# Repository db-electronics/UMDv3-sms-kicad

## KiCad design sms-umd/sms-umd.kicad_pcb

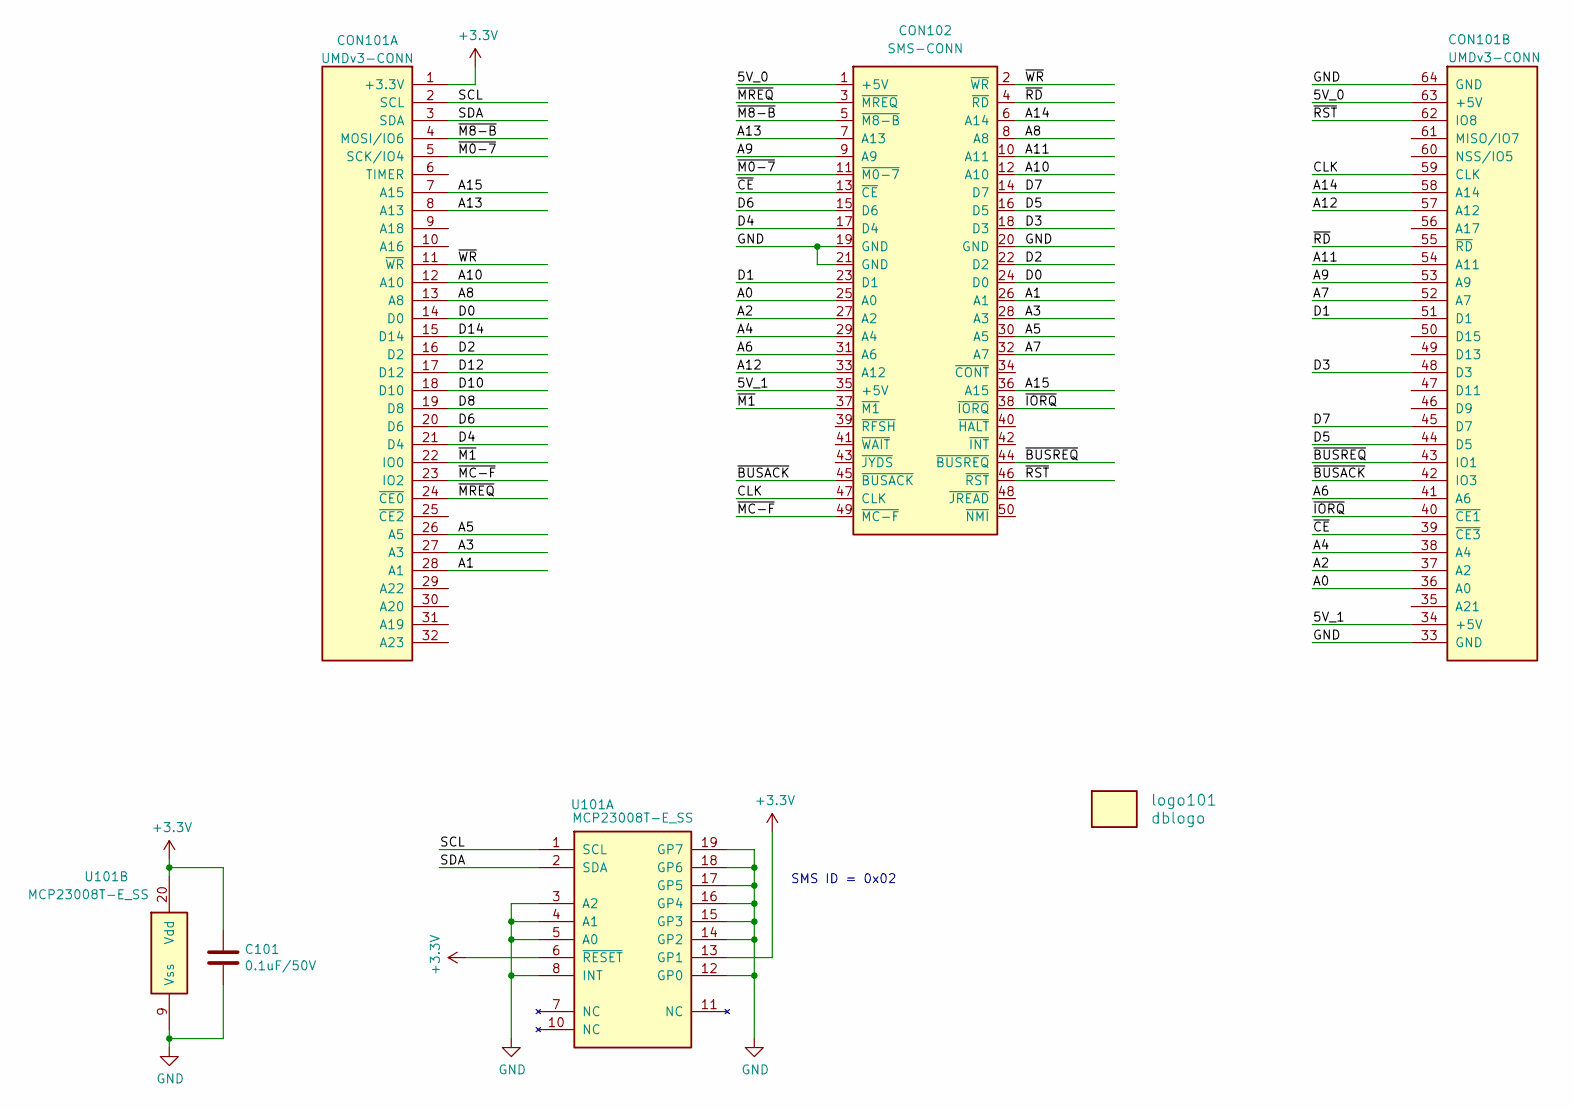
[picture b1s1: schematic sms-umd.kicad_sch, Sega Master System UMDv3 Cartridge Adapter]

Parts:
C101: 0.1uF/50V; 0603; Digikey 478-5052-1-ND
CON101: UMDv3-CONN; UMDv3-CONN-DIP64; Digikey SAM1211-32-ND
CON102: SMS-CONN; Digikey A31718-ND
U101: MCP23008T-E_SS; SSOP-20; Digikey MCP23008T-E/SSCT-ND
logo101: dblogo; db-logo_10mm

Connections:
+3V3: C101.1, CON101.1 (+3.3V), U101.6 (~RESET), U101.13 (GP1), U101.20 (Vdd)
/5V_0: CON101.63 (+5V), CON102.1 (+5V)
/5V_1: CON101.34 (+5V), CON102.35 (+5V)
/A0: CON101.36 (A0), CON102.25 (A0)
/A1: CON101.28 (A1), CON102.26 (A1)
/A2: CON101.37 (A2), CON102.27 (A2)
/A3: CON101.27 (A3), CON102.28 (A3)
/A4: CON101.38 (A4), CON102.29 (A4)
/A5: CON101.26 (A5), CON102.30 (A5)
/A6: CON101.41 (A6), CON102.31 (A6)
/A7: CON101.52 (A7), CON102.32 (A7)
/A8: CON101.13 (A8), CON102.8 (A8)
/A9: CON101.53 (A9), CON102.9 (A9)
/A10: CON101.12 (A10), CON102.12 (A10)
/A11: CON101.54 (A11), CON102.10 (A11)
/A12: CON101.57 (A12), CON102.33 (A12)
/A13: CON101.8 (A13), CON102.7 (A13)
/A14: CON101.58 (A14), CON102.6 (A14)
/A15: CON101.7 (A15), CON102.36 (A15)
/CLK: CON101.59 (CLK), CON102.47 (CLK)
/D0: CON101.14 (D0), CON102.24 (D0)
/D1: CON101.51 (D1), CON102.23 (D1)
/D2: CON101.16 (D2), CON102.22 (D2)
/D3: CON101.48 (D3), CON102.18 (D3)
/D4: CON101.21 (D4), CON102.17 (D4)
/D5: CON101.44 (D5), CON102.16 (D5)
/D6: CON101.20 (D6), CON102.15 (D6)
/D7: CON101.45 (D7), CON102.14 (D7)
/D8: CON101.19 (D8)
/D10: CON101.18 (D10)
/D12: CON101.17 (D12)
/D14: CON101.15 (D14)
/SCL: CON101.2 (SCL), U101.1 (SCL)
/SDA: CON101.3 (SDA), U101.2 (SDA)
/~BUSACK: CON101.42 (IO3), CON102.45 (~BUSACK)
/~BUSREQ: CON101.43 (IO1), CON102.44 (~BUSREQ)
/~CE: CON101.39 (~CE3), CON102.13 (~CE)
/~IORQ: CON101.40 (~CE1), CON102.38 (~IORQ)
/~M0-7: CON101.5 (SCK/IO4), CON102.11 (~M0-7)
/~M1: CON101.22 (IO0), CON102.37 (~M1)
/~M8-B: CON101.4 (MOSI/IO6), CON102.5 (~M8-B)
/~MC-F: CON101.23 (IO2), CON102.49 (~MC-F)
/~MREQ: CON101.24 (~CE0), CON102.3 (~MREQ)
/~RD: CON101.55 (~RD), CON102.4 (~RD)
/~RST: CON101.62 (IO8), CON102.46 (~RST)
/~WR: CON101.11 (~WR), CON102.2 (~WR)
GND: C101.2, CON101.33 (GND), CON101.64 (GND), CON102.19 (GND), CON102.20 (GND), CON102.21 (GND), U101.3 (A2), U101.4 (A1), U101.5 (A0), U101.8 (INT), U101.9 (Vss), U101.12 (GP0), U101.14 (GP2), U101.15 (GP3), U101.16 (GP4), U101.17 (GP5), U101.18 (GP6), U101.19 (GP7)

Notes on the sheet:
SMS ID = 0x02

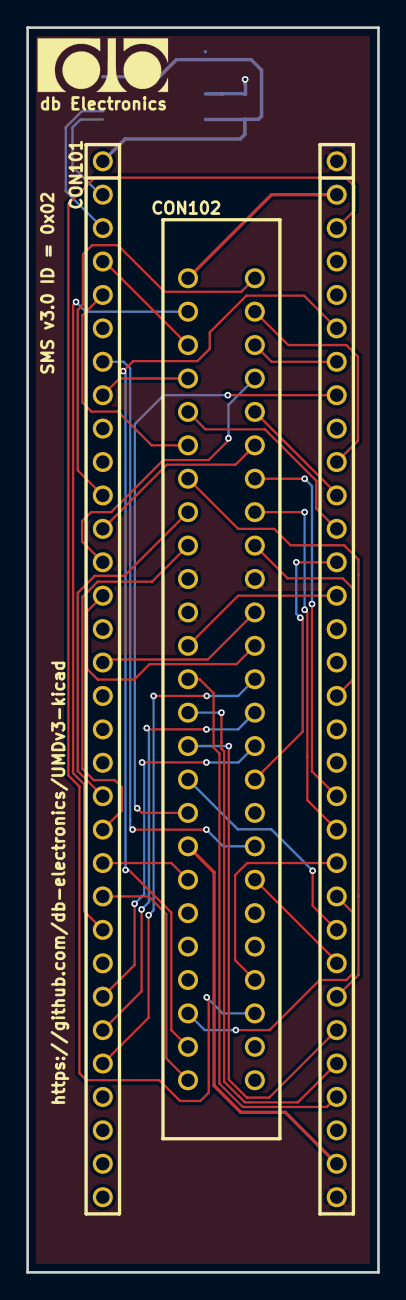
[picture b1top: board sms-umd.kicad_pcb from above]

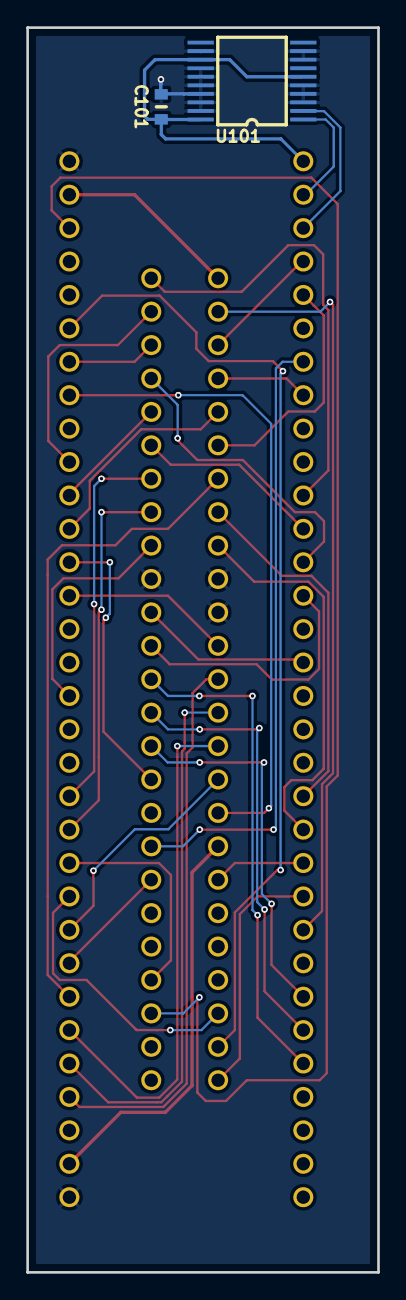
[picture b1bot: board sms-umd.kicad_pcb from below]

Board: 2 copper layers, 26.7 x 94.6 mm, 5 parts (2 on the bottom side), 43 nets.

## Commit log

2023-11-10 adding license files
2023-11-17 added KiCad project files
2023-12-20 version 3.0

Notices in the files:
sms-umd/sms-umd.kicad_pcb:
Licensed Under CERN OHL v.1.2
sms-umd/sms-umd.kicad_sch:
Copyright René Richard 2023
